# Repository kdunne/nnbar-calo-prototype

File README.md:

# nnbar-calo-prototype

Readout electronics for NNBAR calorimeter prototype at SU
Uses KiCAD version 5

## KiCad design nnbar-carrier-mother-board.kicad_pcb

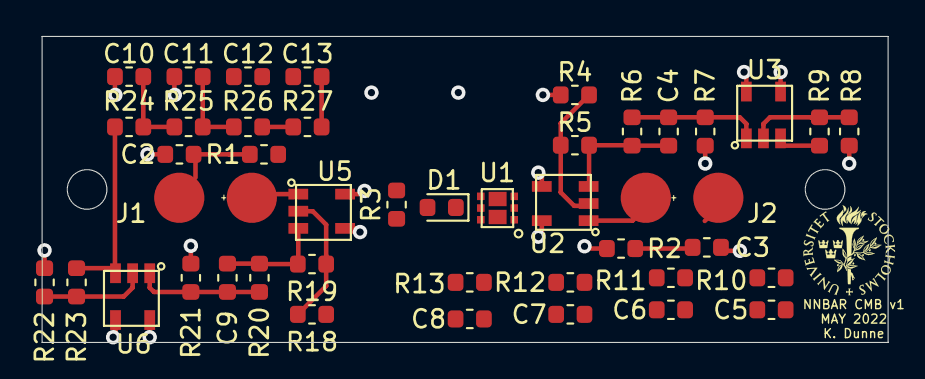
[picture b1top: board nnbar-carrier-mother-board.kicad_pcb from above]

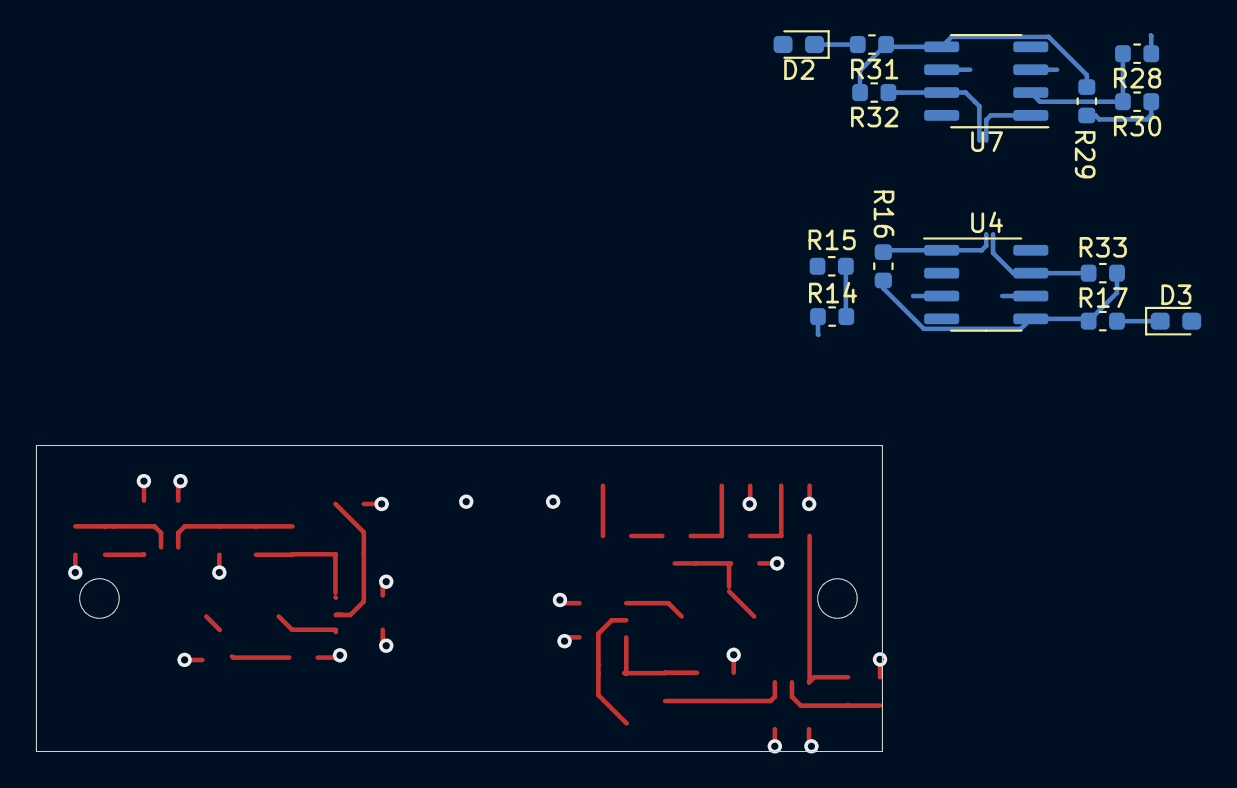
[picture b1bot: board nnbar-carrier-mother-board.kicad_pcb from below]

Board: 4 copper layers, 47.0 x 17.0 mm, 57 parts (14 on the bottom side), 40 nets.

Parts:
C2, C3: C_Small; C_0603_1608Metric
C4, C9: 20p; C_0603_1608Metric
C5, C6, C7, C8, C10, C11, C12, C13: 500p; C_0603_1608Metric
D1: LED; D_0603_1608Metric
D2, D3: D_Zener; D_0603_1608Metric_Pad1.05x0.95mm_HandSolder
J1, J2: POGO PINS; POGO
R1, R2, R3: R_Small; R_0603_1608Metric
R4, R18: 51; R_0603_1608Metric
R5, R8, R14, R19, R22, R28: 1k; R_0603_1608Metric
R6, R20: 2200; R_0603_1608Metric
R7, R21: 220; R_0603_1608Metric
R9, R23: 18k; R_0603_1608Metric
R10, R11, R12, R13, R24, R25, R26, R27: 20; R_0603_1608Metric
R15, R30: 10k; R_0603_1608Metric
R16, R17, R29, R31, R32, R33: 100; R_0603_1608Metric
U1: FDFMA3N109
U2, U3, U5, U6: OPAMP; OPA846
U4, U7: AD8039; SOIC-8_3.9x4.9mm_P1.27mm

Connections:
+48V: R1.2, R2.2
/SIPM1/+5V: U5.4, U6.4
/SIPM1/-5V: D2.2, U5.5, U6.5, U7.4
/SIPM1/FILTER_OUT_1: C13.1, R27.2, U7.3
/SIPM2/+5V: U2.4, U3.4
/SIPM2/-5V: D3.2, U2.5, U3.5, U4.4
/SIPM2/FILTER_OUT_2: C8.1, R13.2, U4.3
/SIPM_1_BIAS: C2.1, J1.1, R1.1
/SIPM_1_N: R32.1, U7.7
/SIPM_1_OUT: J1.2, U5.1
/SIPM_1_P: R29.2, R30.1, U7.1
/SIPM_2_BIAS: C3.1, J2.1, R2.1
/SIPM_2_N: R33.1, U4.7
/SIPM_2_OUT: J2.2, U2.1
/SIPM_2_P: R15.1, R16.2, U4.1
GND: C2.2, C3.2, C5.2, C6.2, C7.2, C8.2, C10.2, C11.2, C12.2, C13.2, R4.2, R7.2, R8.2, R14.2, R18.2, R21.2, R22.2, R28.2, U1.4, U4.6, U7.6
unnamed: C4.1, R5.1, R6.1, U2.3
unnamed: C4.2, R6.2, R7.1, U3.1
unnamed: C5.1, R10.2, R11.1
unnamed: C6.1, R11.2, R12.1
unnamed: C7.1, R12.2, R13.1
unnamed: C9.1, R19.1, R20.1, U5.3
unnamed: C9.2, R20.2, R21.1, U6.1
unnamed: C10.1, R24.2, R25.1
unnamed: C11.1, R25.2, R26.1
unnamed: C12.1, R26.2, R27.1
unnamed: D1.1, U1.3
unnamed: D1.2, R3.1
unnamed: D2.1, R31.2
unnamed: D3.1, R17.2
unnamed: R4.1, R5.2, U2.2
unnamed: R8.1, R9.2, U3.2
unnamed: R9.1, R10.1, U3.3
unnamed: R14.1, R15.2, U4.2
unnamed: R16.1, R17.1, R33.2, U4.5
unnamed: R18.1, R19.2, U5.2
unnamed: R22.1, R23.2, U6.2
unnamed: R23.1, R24.1, U6.3
unnamed: R28.1, R30.2, U7.2
unnamed: R29.1, R31.1, R32.2, U7.5

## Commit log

2021-07-12 Add design files from local repo
2021-11-12 v1 - four stage filter
2022-02-03 Add SPICE files
2022-03-31 Updated to AD8039 quad opamp
2022-08-01 update pcb with vertical sipms
2022-12-12 Add lib-table
2022-12-13 Add FDFMA3N109 footprint to repo
2022-12-13 Migrate to KiCAD v6
